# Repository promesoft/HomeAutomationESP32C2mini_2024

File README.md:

# HomeAutomationESP32C2mini_2024
 Kicad 8

# Purpose
Use for testing ESP32 C3 as replacement for ESP 8266 in ESP Home config

| ESP Designation  | Pin | Use |
| ------------- | ------------- | ------------- |
| U201 ESP32 C3 |  |   |
| U301 ESP32 C3 |  |   |
| U401 ESP32 C3 |  |   |
| U501 ESP32 C3 |  |   |
| U601 ESP32 C3 |  |   |
| U701 ESP8266 | D1 | SCL AM2320 |
| U701 ESP8266 | D2 | SDA AM2320 |
| U701 ESP8266 | D3 / GPIO0| LED |
| U701 ESP8266 | D4 / GPIO2| 18B20 / Onboard LED|

# Status - Preliminary mounted
## Initial 
| Stage  | Detail | Status |
| ------------- | ------------- | ------------- |
| create material  | sch/pcb | OK  |
| | gerber | OK |
| production  |   | ok |
|  | produced | ok |
|  | delivered | ok |
## Preliminary validation
| Test  | Detail | Status |
| ------------- | ------------- | ------------- |
| Initial Inspection | | OK |
| Initial Technical Test |  |  |
| Initial Technical Test |  |  |
| Initial Technical Test |  |  |
| Initial Product Test |  |  |
| Initial Product Test |  |  |
| Initial Product Test |  |  |
| Power Draw |  |  |
| Power Draw |  |  |
| Power Draw |  |  |

## Secondary validation
| Test  | Detail | Status |
| ------------- | ------------- |------------- |
| Product Test |  | |
| Product Test |  |  |
| Quality | | |
| Quality | | |
| Long Term Product Test |  |  |
| Power Draw |  |  |
| Power Draw |  |  |
| Power Draw |  |  |

## Errata
### Errata - Sub 1
### Errata - Sub 2
### Errata - Sub 3

## Issues and Notes
### Sub 1
### Sub 2

# Pictures

# Inspiration
## ATMega 32A
https://github.com/MCUdude/MightyCore

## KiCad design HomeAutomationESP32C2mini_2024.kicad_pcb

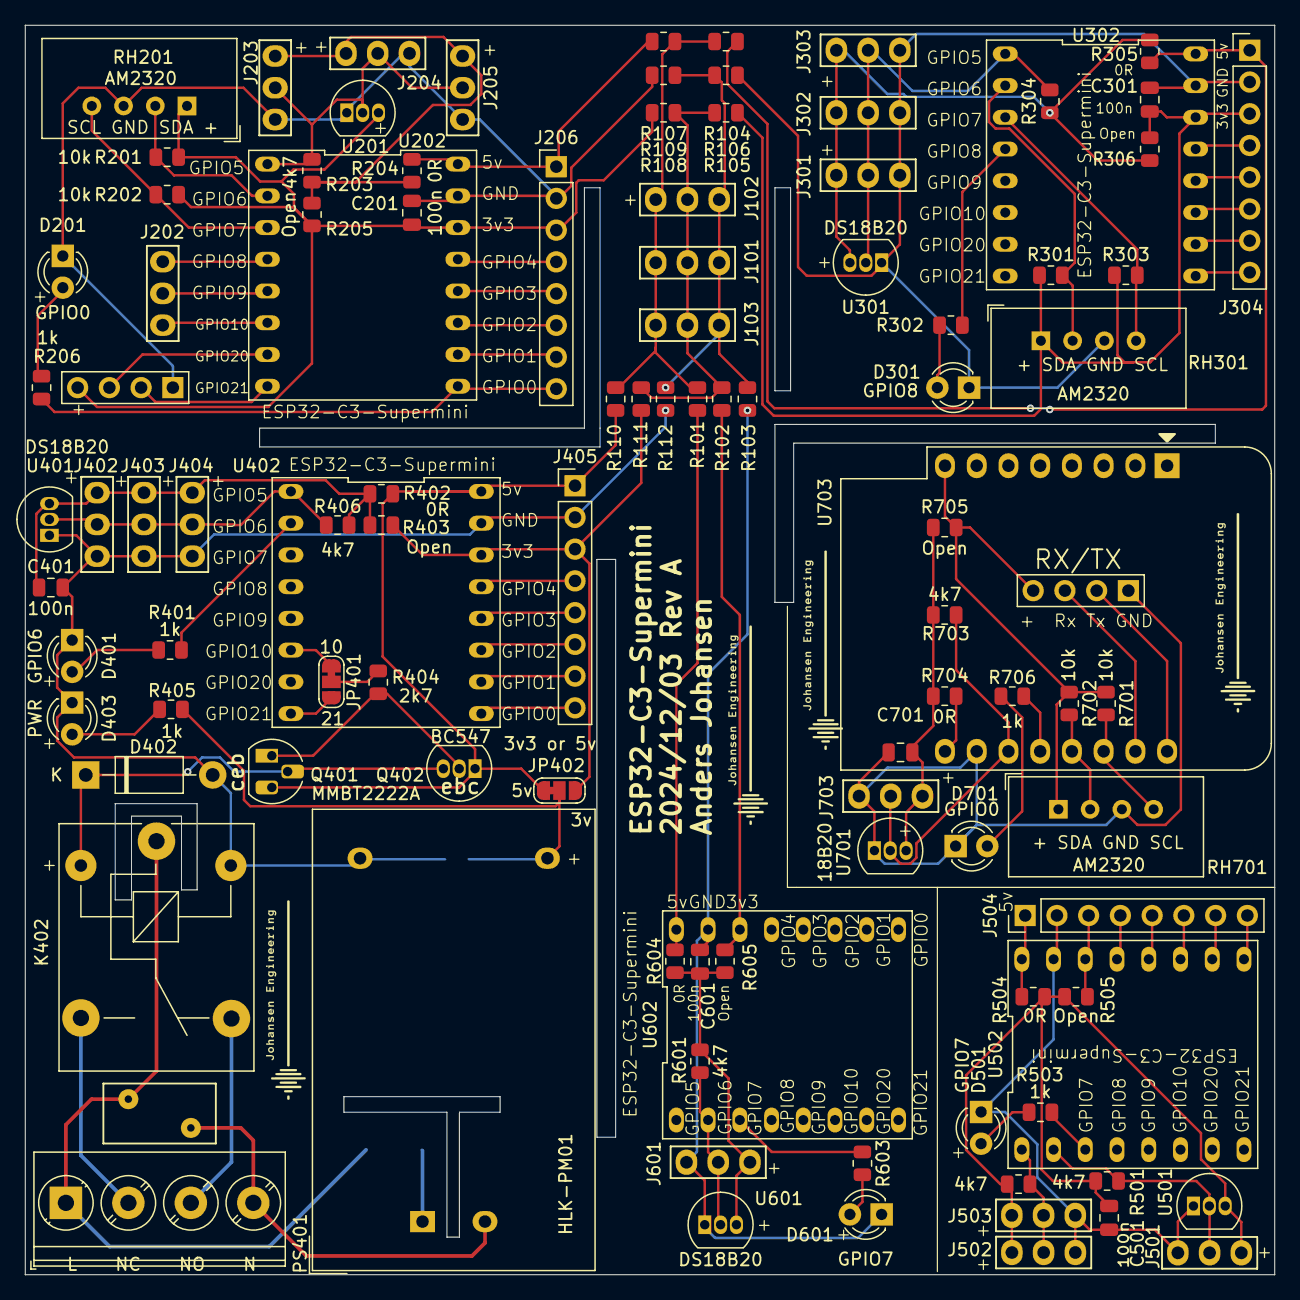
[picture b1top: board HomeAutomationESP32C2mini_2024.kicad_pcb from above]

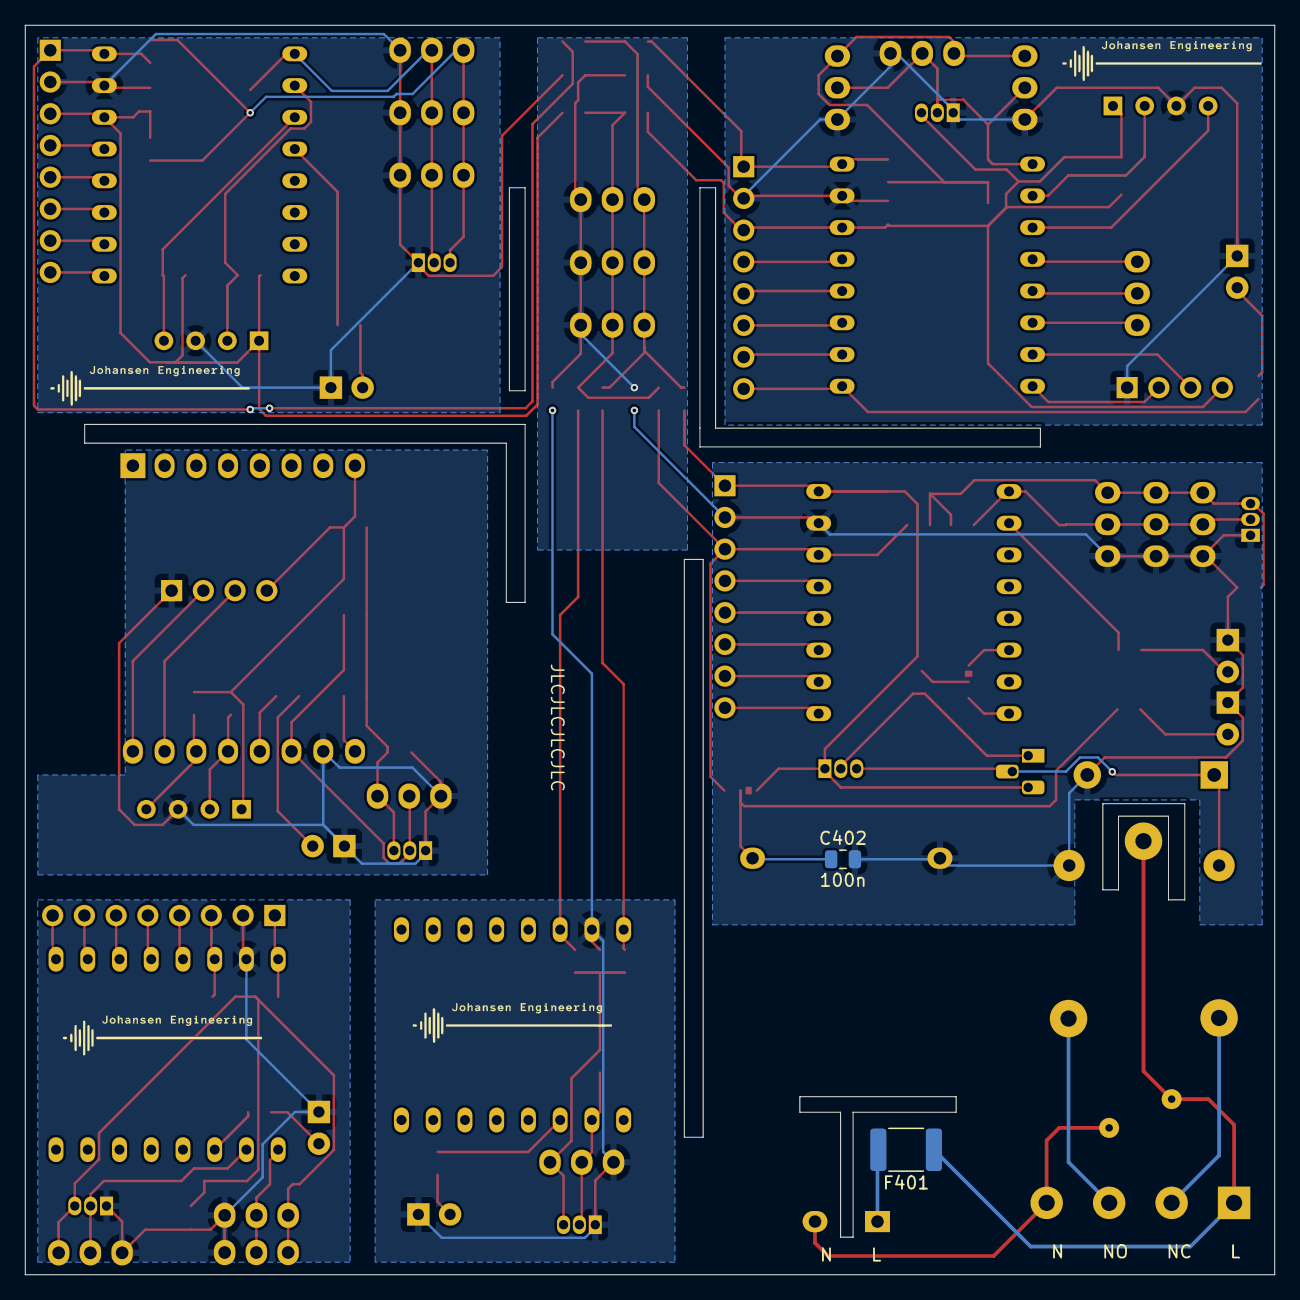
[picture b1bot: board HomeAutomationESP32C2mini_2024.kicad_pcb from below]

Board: 2 copper layers, 100.0 x 100.0 mm, 108 parts (2 on the bottom side), 90 nets.

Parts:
C201, C301, C401, C402, C501, C601, C701: 100n; C_0805_2012Metric
D201, D701: GPIO0; LED_D3.0mm
D301: GPIO8; LED_D3.0mm
D401: GPIO6; LED_D3.0mm
D402: DIODE; D_DO-41_SOD81_P10.16mm_Horizontal
D403: PWR; LED_D3.0mm
D501, D601: GPIO7; LED_D3.0mm
F401: Polyfuse_Small; Fuse_1812_4532Metric_Pad1.30x3.40mm_HandSolder
J101, J102, J103: Conn_01x03; Pins_1x03_2.54mm_TH
J201, J701: RX/TX; Pins_1x04_2.54mm_TH
J202: IO8-10; Pins_1x03_2.54mm_TH
J203, J204, J205, J301, J302, J303, J402, J403, J404, J501, J502, J503, J601, J703: 18B20; Pins_1x03_2.54mm_TH
J206, J304, J405, J504: IO; Pins_1x08_2.54mm_TH
J401: 230V; TerminalBlock_Phoenix_PT-1,5-4-5.0-H_1x04_P5.00mm_Horizontal
JP401: IO10 or 21; SolderJumper-3_P1.3mm_Bridged12_RoundedPad1.0x1.5mm_NumberL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
JP402: 3v3 or 5v; SolderJumper-3_P1.3mm_Bridged12_RoundedPad1.0x1.5mm_NumberL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
K402: SANYOU_SRD_Form_C; Relay_SPDT_SANYOU_SRD_Series_Form_C
PS401: HLK-PM01; Converter_ACDC_Hi-Link_HLK-PMxx
Q401: MMBT2222A; TO-92_HandSolder
Q402: BC547; TO-92_Inline
R101, R102, R103, R104, R105, R106, R107, R108, R109, R110, R111, R112, R204, R305, R402, R504, R604, R704: 0R; R_0805_2012Metric
R201, R202, R301, R303, R701, R702: 10k; R_0805_2012Metric
R203, R304, R406, R501, R502, R601, R703: 4k7; R_0805_2012Metric
R205, R306, R403, R505, R605, R705: Open; R_0805_2012Metric
R206, R302, R401, R405, R503, R603, R706: 1k; R_0805_2012Metric
R404: 2k7; R_0805_2012Metric
RH201, RH301, RH701: AM2320; ASAIR_AM2302_P2.54mm_Vertical
RV401: Varistor; RV_Disc_D9mm_W4.8mm_P5mm
U201, U301, U401, U501, U601, U701: DS18B20; TO-92_Inline
U202, U302, U402, U502, U602: ESP32-C3-Supermini
U703: WeMos_D1_mini; WEMOS_D1_mini_light

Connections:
+3.3V: J101.2, J102.2, J103.2, R102.2 (-), R105.2 (-), R108.2 (-), R111.2 (-)
+5V: J101.3, J102.3, J103.3, R101.2 (-), R104.2 (-), R107.2 (-), R110.2 (-)
/ESP32-C3-supermini-4/+3v3: R102.1 (+), R605.2 (-), U602.14 (3v3)
/ESP32-C3-supermini-4/+5V: R101.1 (+), R604.2 (-), U602.16 (5V)
/ESP32-C3-supermini-4/GND: C601.2 (-), D601.1 (K), J601.1, R103.1 (+), U601.1 (GND), U602.15 (GND)
/ESP32C3-Supermini-1/+3v3: C201.1 (+), J201.4, J206.3, R108.1 (+), R201.1 (+), R202.1 (+), R205.2 (-), RH201.1 (VDD), U201.3 (V_{DD}), U202.14 (3v3)
/ESP32C3-Supermini-1/+5V: J206.1, R107.1 (+), R204.2 (-), U202.16 (5V)
/ESP32C3-Supermini-1/GND: C201.2 (-), D201.1 (K), J201.1, J203.3, J204.3, J205.3, J206.2, R109.1 (+), RH201.3 (GND), U201.1 (GND), U202.15 (GND)
/ESP32C3-Supermini-2/+3v3: C301.1 (+), J304.3, R105.1 (+), R301.1 (+), R303.1 (+), R306.2 (-), RH301.1 (VDD), U302.14 (3v3)
/ESP32C3-Supermini-2/+5V: J304.1, R104.1 (+), R305.2 (-), U302.16 (5V)
/ESP32C3-Supermini-2/GND: C301.2 (-), D301.1 (K), J301.3, J302.3, J303.3, J304.2, R106.1 (+), RH301.3 (GND), U301.1 (GND), U302.15 (GND)
/ESP32C3_Power/230v_IN: F401.2, PS401.1 (AC/L)
/ESP32C3_Power/230v_NC: J401.2, K402.3
/ESP32C3_Power/230v_NO: J401.3, K402.4
/ESP32C3_Power/+3v3: J405.3, JP402.3 (B), R111.1 (+), R403.2 (-), U402.14 (3v3)
/ESP32C3_Power/+5V: J405.1, JP402.1 (A), Q401.3 (C), Q402.1 (C), R110.1 (+), R402.2 (-), U402.16 (5V)
/ESP32C3_Power/GND: C401.2 (-), C402.2 (-), D401.1 (K), D402.2 (A), D403.1 (K), J402.3, J403.3, J404.3, J405.2, K402.5, PS401.3 (-Vout), R112.1 (+), U401.1 (GND), U402.15 (GND)
/ESP32C3_Supermini-3/+3v3: J504.3, R505.2 (-), U502.14 (3v3)
/ESP32C3_Supermini-3/+5V: J504.1, R504.2 (-), U502.16 (5V)
/ESP32C3_Supermini-3/GND: C501.2 (-), D501.1 (K), J501.1, J502.3, J503.3, J504.2, U501.1 (GND), U502.15 (GND)
/ESP_8266_WemosD1Mini/18B20 Signal: J703.2, R703.1 (+), U701.2 (DQ), U703.11 (D4)
/ESP_8266_WemosD1Mini/18B20 VDD: C701.1 (+), J703.3, R703.2 (-), R704.1 (+), R705.1 (+), U701.3 (V_{DD})
/ESP_8266_WemosD1Mini/+3v3: J701.4, R701.1 (+), R702.1 (+), R705.2 (-), RH701.1 (VDD), U703.8 (3V3)
/ESP_8266_WemosD1Mini/+5V: R704.2 (-), U703.9 (5V)
/ESP_8266_WemosD1Mini/GND: C701.2 (-), D701.1 (K), J701.1, J703.1, RH701.3 (GND), U701.1 (GND), U703.10 (GND)
/ESP_8266_WemosD1Mini/SCL: R701.2 (-), RH701.4 (SCL), U703.14 (SCL/D1)
/ESP_8266_WemosD1Mini/SDA: R702.2 (-), RH701.2 (SDA), U703.13 (SDA/D2)
GND: J101.1, J102.1, J103.1, R103.2 (-), R106.2 (-), R109.2 (-), R112.2 (-)
unnamed: C401.1 (+), J402.1, J403.1, J404.1, R402.1 (+), R403.1 (+), R406.1 (+), U401.3 (V_{DD})
unnamed: C402.1 (+), JP402.2 (C), PS401.4 (+Vout), R405.1 (+)
unnamed: C501.1 (+), J501.3, J502.1, J503.1, R501.2 (-), R502.1 (+), R504.1 (+), R505.1 (+), U501.3 (V_{DD})
unnamed: C601.1 (+), J601.3, R601.2 (-), R604.1 (+), R605.1 (+), U601.3 (V_{DD})
unnamed: D201.2 (A), R206.2 (-)
unnamed: D301.2 (A), R302.2 (-)
unnamed: D401.2 (A), R401.2 (-)
unnamed: D402.1 (K), K402.2, Q401.2 (E), Q402.3 (E)
unnamed: D403.2 (A), R405.2 (-)
unnamed: D501.2 (A), R503.2 (-)
unnamed: D601.2 (A), R603.2 (-)
unnamed: D701.2 (A), R706.2 (-)
unnamed: J201.2, U202.8 (GPIO21)
unnamed: J201.3, U202.7 (GPIO20)
unnamed: J202.1, U202.6 (GPIO10)
unnamed: J202.2, U202.5 (GPIO9)
unnamed: J202.3, U202.4 (GPIO8)
unnamed: J203.1, J204.1, J205.1, R203.1 (+), R204.1 (+), R205.1 (+)
unnamed: J203.2, J204.2, J205.2, R203.2 (-), U201.2 (DQ), U202.1 (GPIO5)
unnamed: J206.4, U202.13 (GPIO4)
unnamed: J206.5, U202.12 (GPIO3)
unnamed: J206.6, U202.11 (GPIO2)
unnamed: J206.7, U202.10 (GPIO1)
unnamed: J206.8, R206.1 (+), U202.9 (GPIO0)
unnamed: J301.1, J302.1, J303.1, R304.1 (+), R305.1 (+), R306.1 (+), U301.3 (V_{DD})
unnamed: J301.2, J302.2, J303.2, R304.2 (-), U301.2 (DQ), U302.1 (GPIO5)
unnamed: J304.4, U302.13 (GPIO4)
unnamed: J304.5, U302.12 (GPIO3)
unnamed: J304.6, U302.11 (GPIO2)
unnamed: J304.7, U302.10 (GPIO1)
unnamed: J304.8, U302.9 (GPIO0)
unnamed: J402.2, J403.2, J404.2, R406.2 (-), U401.2 (DQ), U402.1 (GPIO5)
unnamed: J405.4, U402.13 (GPIO4)
unnamed: J405.5, U402.12 (GPIO3)
unnamed: J405.6, U402.11 (GPIO2)
unnamed: J405.7, U402.10 (GPIO1)
unnamed: J405.8, U402.9 (GPIO0)
unnamed: J501.2, R501.1 (+), U501.2 (DQ), U502.2 (GPIO6)
unnamed: J502.2, J503.2, R502.2 (-), U502.1 (GPIO5)
unnamed: J504.4, U502.13 (GPIO4)
unnamed: J504.5, U502.12 (GPIO3)
unnamed: J504.6, U502.11 (GPIO2)
unnamed: J504.7, U502.10 (GPIO1)
unnamed: J504.8, U502.9 (GPIO0)
unnamed: J601.2, R601.1 (+), U601.2 (DQ), U602.2 (GPIO6)
unnamed: J701.2, U703.16 (TX)
unnamed: J701.3, U703.15 (RX)
unnamed: JP401.1 (A), U402.6 (GPIO10)
unnamed: JP401.3 (B), U402.8 (GPIO21)
unnamed: JP401.2 (C), R404.1 (+)
unnamed: Q401.1 (B), Q402.2 (B), R404.2 (-)
unnamed: R201.2 (-), RH201.2 (SDA), U202.2 (GPIO6)
unnamed: R202.2 (-), RH201.4 (SCL), U202.3 (GPIO7)
unnamed: R301.2 (-), RH301.2 (SDA), U302.2 (GPIO6)
unnamed: R302.1 (+), U302.4 (GPIO8)
unnamed: R303.2 (-), RH301.4 (SCL), U302.3 (GPIO7)
unnamed: R401.1 (+), U402.2 (GPIO6)
unnamed: R503.1 (+), U502.3 (GPIO7)
unnamed: R603.1 (+), U602.3 (GPIO7)
unnamed: R706.1 (+), U703.12 (D3)
V-L: F401.1, J401.1, K402.1, RV401.1
V-N: J401.4, PS401.2 (AC/N), RV401.2

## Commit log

2024-12-30 Update README.md
    Template
2024-12-30 board pic
2024-12-30 Update README.md
    HomeAutomationESP32C2mini_2024.jpg
2025-01-26 Picture Updates
2025-02-09 Update README.md
    Assembled board pic
